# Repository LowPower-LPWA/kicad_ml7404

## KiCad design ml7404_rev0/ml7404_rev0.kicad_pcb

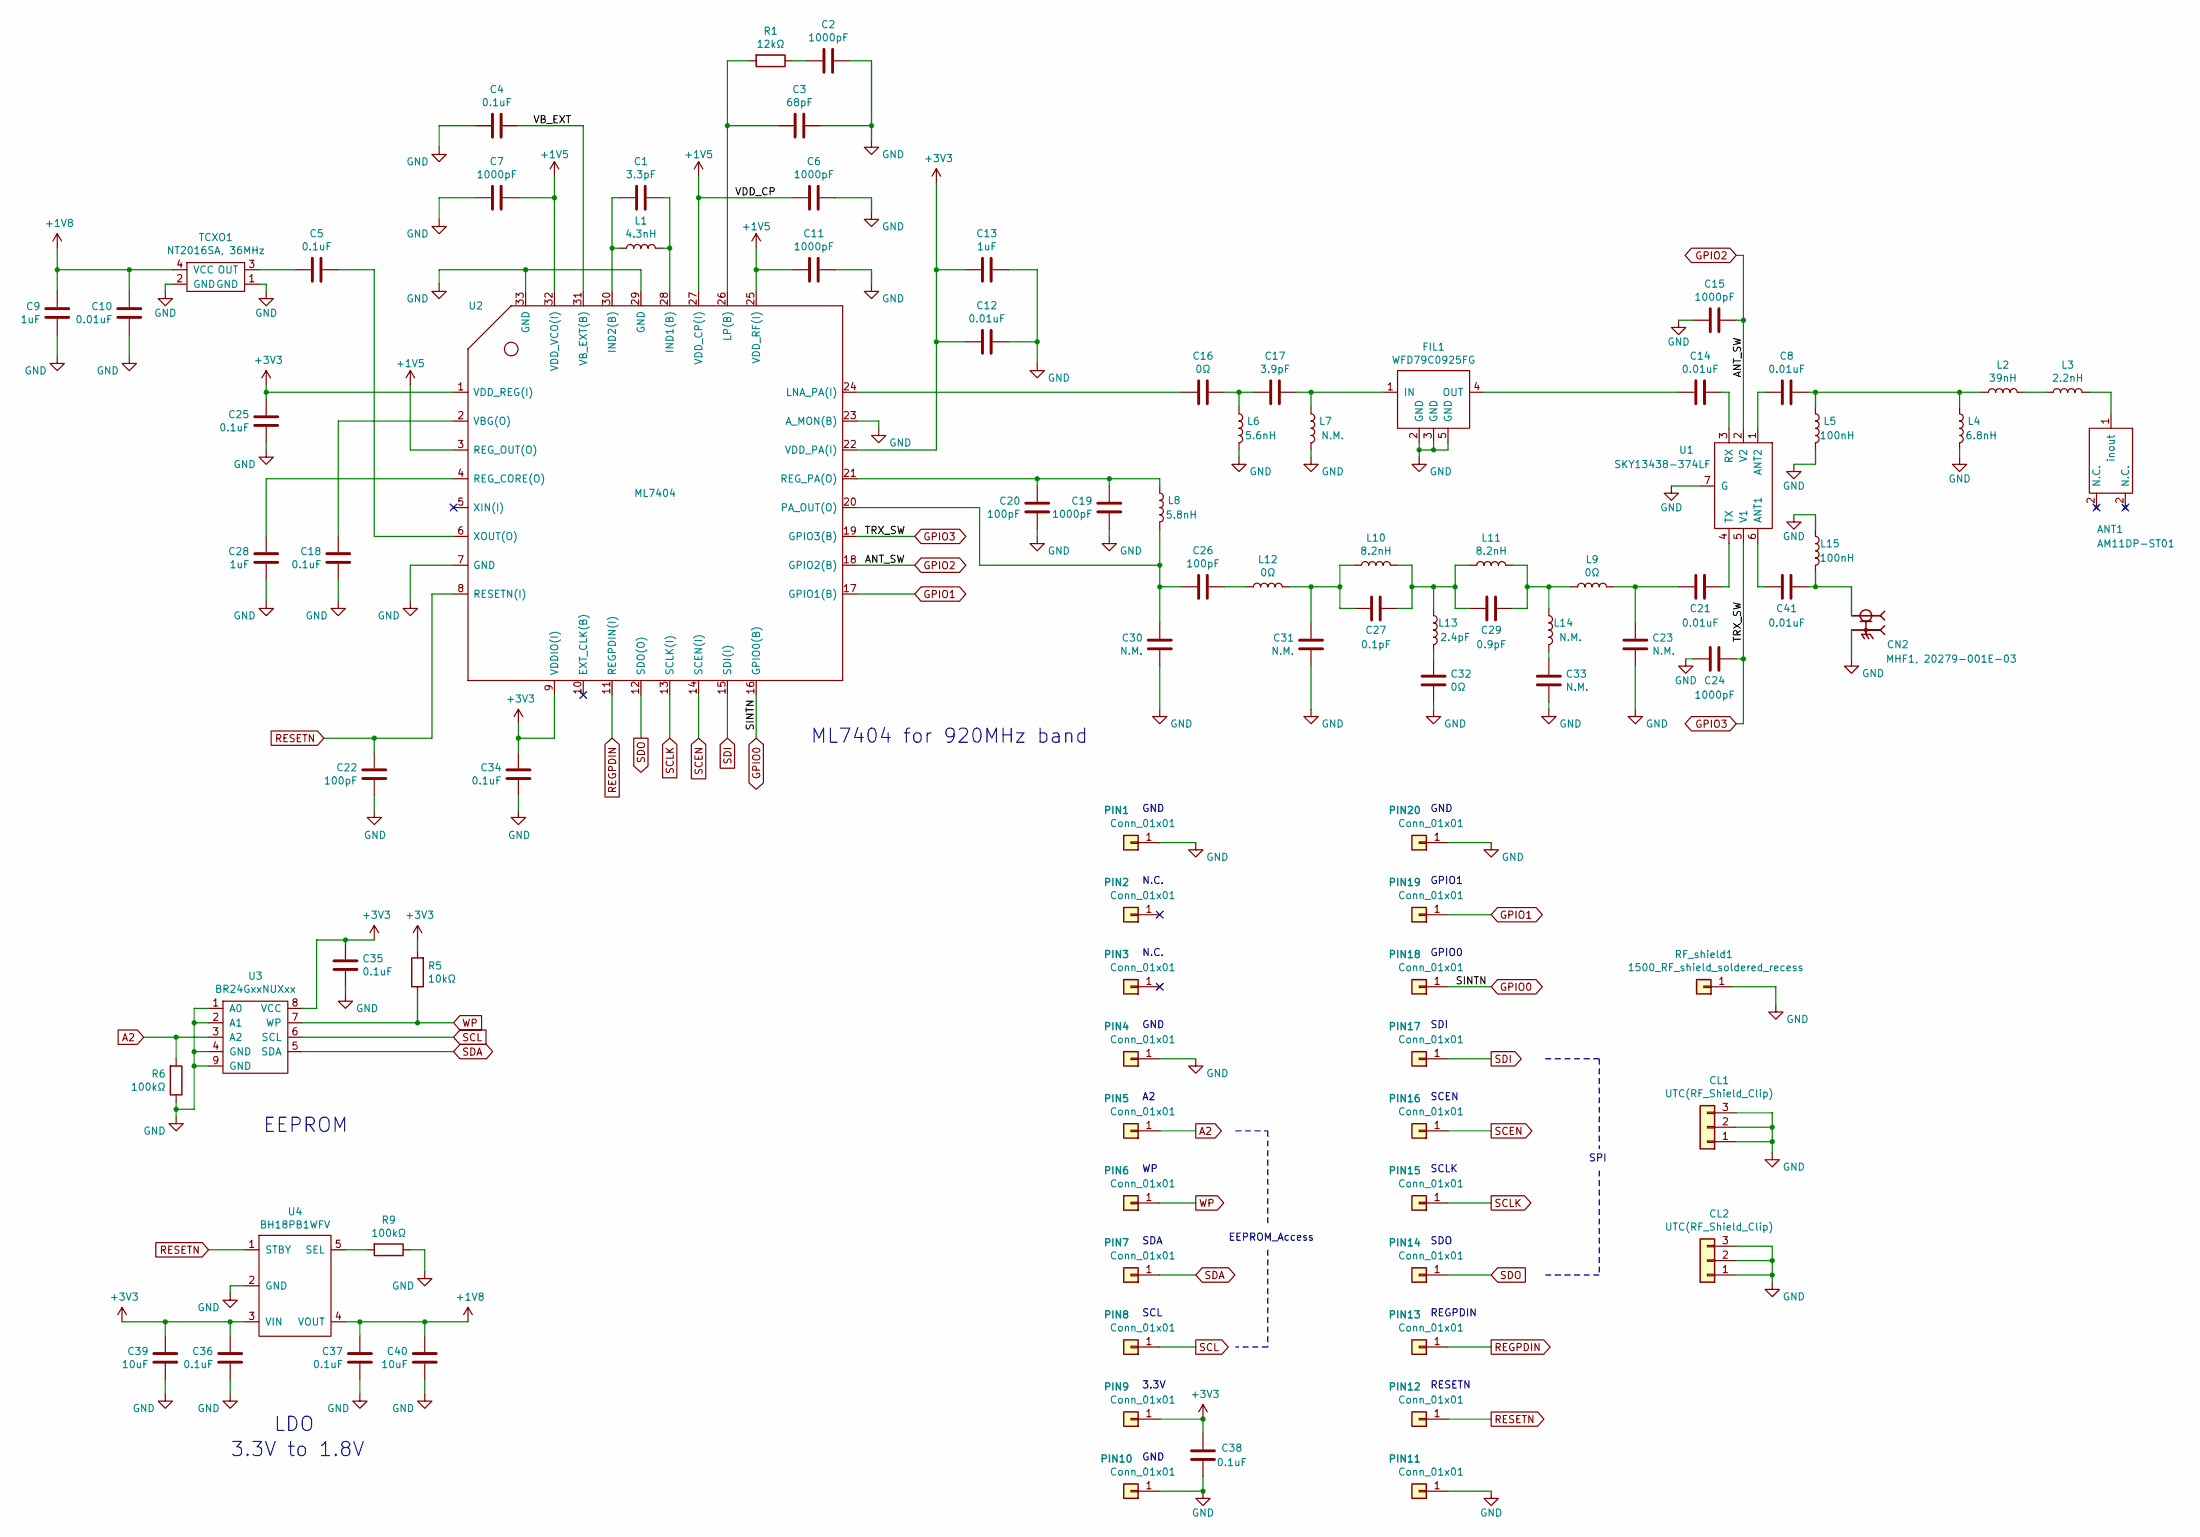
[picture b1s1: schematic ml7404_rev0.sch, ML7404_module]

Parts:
ANT1: AM11DP-ST01
C1: 3.3pF; C_0402_1005Metric
C2, C6, C7, C11: 1000pF; C_0402_1005Metric
C3: 68pF; C_0402_1005Metric
C4, C5, C18, C25, C34, C35, C36, C37, C38: 0.1uF; C_0402_1005Metric
C8, C14, C21, C41: 0.01uF; C_0201_0603Metric
C9, C13, C28: 1uF; C_0402_1005Metric
C10, C12: 0.01uF; C_0402_1005Metric
C15, C19, C24: 1000pF; C_0201_0603Metric
C16, C32: 0Ω; C_0201_0603Metric
C17: 3.9pF; C_0201_0603Metric
C20, C26: 100pF; C_0201_0603Metric
C22: 100pF; C_0402_1005Metric
C23, C30, C31, C33: N.M.; C_0201_0603Metric
C27: 0.1pF; C_0201_0603Metric
C29: 0.9pF; C_0201_0603Metric
C39, C40: 10uF; C_0603_1608Metric
CL1, CL2: UTC(RF_Shield_Clip); UTC_RF_Shield_Clip
CN2: MHF1, 20279-001E-03; IPEX_20279-001E-03
FIL1: WFD79C0925FG
L1: 4.3nH; L_0402_1005Metric
L2: 39nH; L_0201_0603Metric
L3: 2.2nH; L_0201_0603Metric
L4: 6.8nH; L_0201_0603Metric
L5, L15: 100nH; L_0201_0603Metric
L6: 5.6nH; L_0201_0603Metric
L7, L14: N.M.; L_0201_0603Metric
L8: 5.8nH; L_0201_0603Metric
L9, L12: 0Ω; L_0201_0603Metric
L10, L11: 8.2nH; L_0201_0603Metric
L13: 2.4pF; L_0201_0603Metric
PIN1, PIN2, PIN3, PIN4, PIN5, PIN6, PIN7, PIN8, PIN9, PIN10, PIN11, PIN12, PIN13, PIN14, PIN15, PIN16, PIN17, PIN18, PIN19, PIN20: Conn_01x01; terminal
R1: 12kΩ; R_0402_1005Metric
R5: 10kΩ; R_0402_1005Metric
R6, R9: 100kΩ; R_0402_1005Metric
RF_shield1: 1500_RF_shield_soldered_recess; 1500_RF_Shield_soldered_30mmx25mm
TCXO1: NT2016SA, 36MHz; TCXO_2016SA
U1: SKY13438-374LF
U2: ML7404; ml7404
U3: BR24GxxNUXxx
U4: BH18PB1WFV; BH18PB1WHFV

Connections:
+1V5: C6.2, C7.1, C11.2, U2.3 (REG_OUT(O)), U2.25 (VDD_RF(I)), U2.27 (VDD_CP(I)), U2.32 (VDD_VCO(I))
+1V8: C9.2, C10.2, C37.2, C40.2, TCXO1.4 (VCC), U4.4 (VOUT)
+3V3: C12.2, C13.2, C25.2, C34.2, C35.2, C36.2, C38.2, C39.2, PIN9.1, R5.2, U2.1 (VDD_REG(I)), U2.9 (VDDIO(I)), U2.22 (VDD_PA(I)), U3.8 (VCC), U4.3 (VIN)
/VB_EXT: C4.1, U2.31 (VB_EXT(B))
A2: PIN5.1, R6.2, U3.3 (A2)
GND: C2.1, C3.1, C4.2, C6.1, C7.2, C9.1, C10.1, C11.1, C12.1, C13.1, C15.2, C18.1, C19.1, C20.1, C22.1, C23.1, C24.2, C25.1, C28.1, C30.1, C31.1, C32.1, C33.1, C34.1, C35.1, C36.1, C37.1, C38.1, C39.1, C40.1, CL1.1, CL1.2, CL1.3, CL2.1, CL2.2, CL2.3, CN2.2, CN2.3, FIL1.2 (GND), FIL1.3 (GND), FIL1.5 (GND), L4.2, L5.2, L6.2, L7.2, L15.1, PIN1.1, PIN4.1, PIN10.1, PIN11.1, PIN20.1, R6.1, R9.1, RF_shield1.1, TCXO1.1 (GND), TCXO1.2 (GND), U1.7 (G), U2.7 (GND), U2.23 (A_MON(B)), U2.29 (GND), U2.33 (GND), U3.1 (A0), U3.2 (A1), U3.4 (GND), U3.9 (GND), U4.2 (GND)
GPIO0: PIN18.1, U2.16 (GPIO0(B))
GPIO1: PIN19.1, U2.17 (GPIO1(B))
GPIO2: C15.1, U1.2 (V2), U2.18 (GPIO2(B))
GPIO3: C24.1, U1.5 (V1), U2.19 (GPIO3(B))
unnamed: ANT1.1 (inout), L3.2
unnamed: C1.1, L1.2, U2.28 (IND1(B))
unnamed: C1.2, L1.1, U2.30 (IND2(B))
unnamed: C2.2, R1.1
unnamed: C3.2, R1.2, U2.26 (LP(B))
unnamed: C5.1, U2.6 (XOUT(O))
unnamed: C5.2, TCXO1.3 (OUT)
unnamed: C8.1, L2.1, L4.1, L5.1
unnamed: C8.2, U1.1 (ANT2)
unnamed: C14.1, U1.3 (RX)
unnamed: C14.2, FIL1.4 (OUT)
unnamed: C16.1, C17.2, L6.1
unnamed: C16.2, U2.24 (LNA_PA(I))
unnamed: C17.1, FIL1.1 (IN), L7.1
unnamed: C18.2, U2.2 (VBG(O))
unnamed: C19.2, C20.2, L8.1, U2.21 (REG_PA(O))
unnamed: C21.1, U1.4 (TX)
unnamed: C21.2, C23.2, L9.2
unnamed: C26.1, L12.1
unnamed: C26.2, C30.2, L8.2, U2.20 (PA_OUT(O))
unnamed: C27.1, C29.2, L10.2, L11.1, L13.1
unnamed: C27.2, C31.2, L10.1, L12.2
unnamed: C28.2, U2.4 (REG_CORE(O))
unnamed: C29.1, L9.1, L11.2, L14.1
unnamed: C32.2, L13.2
unnamed: C33.2, L14.2
unnamed: C41.1, CN2.1, L15.2
unnamed: C41.2, U1.6 (ANT1)
unnamed: L2.2, L3.1
unnamed: R9.2, U4.5 (SEL)
REGPDIN: PIN13.1, U2.11 (REGPDIN(I))
RESETN: C22.2, PIN12.1, U2.8 (RESETN(I)), U4.1 (STBY)
SCEN: PIN16.1, U2.14 (SCEN(I))
SCL: PIN8.1, U3.6 (SCL)
SCLK: PIN15.1, U2.13 (SCLK(I))
SDA: PIN7.1, U3.5 (SDA)
SDI: PIN17.1, U2.15 (SDI(I))
SDO: PIN14.1, U2.12 (SDO(O))
WP: PIN6.1, R5.1, U3.7 (WP)

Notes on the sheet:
N.C.
GND
SCL
SDA
3.3V
EEPROM_Access
EEPROM
LDO
3.3V to 1.8V
ML7404 for 920MHz band
SCEN
SPI
GPIO1
GPIO0
SDI
SCLK
SDO
REGPDIN
RESETN

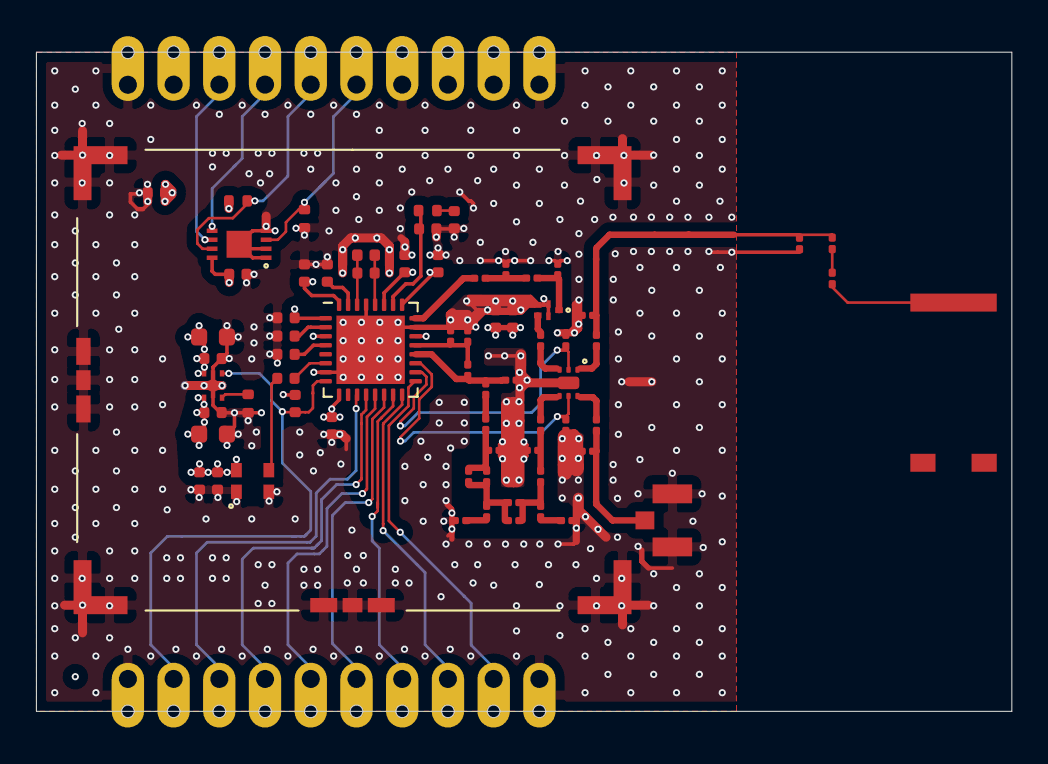
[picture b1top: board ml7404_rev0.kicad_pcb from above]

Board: 4 copper layers, 54.2 x 36.6 mm, 91 parts (0 on the bottom side), 49 nets.

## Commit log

2021-02-28 just create project
2021-03-21 Pre layout
2021-03-24 adjusted RF shield footprint
2021-03-24 added L4 mask
2021-03-25 .gitignoreに不要なファイルを追加
2021-04-10 pre layout2
2021-05-05 Minor change (Add GND VIA)
2021-05-05 Change RF SMD size 0603
